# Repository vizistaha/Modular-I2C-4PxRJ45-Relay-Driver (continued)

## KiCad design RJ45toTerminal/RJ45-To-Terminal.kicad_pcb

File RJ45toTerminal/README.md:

# RJ45 To Terminal Mapping

| Pin        | Pair       | Color        | Terminal  | 
| ---------- |:----------:| ------------ | --------- | 
| 1          | 1+         | Orange-White | 1         | 
| 2          | 1-         | Orange       | 2         |
| 3          | 2+         | Green-White  | 3         |
| 6          | 2-         | Green        | 4         |
| 5          | 3+         | Blue-White   | 5         |
| 4          | 3-         | Blue         | 6         |
| 7          | 4+         | Brown-White  | 7         |
| 8          | 4-         | Brown        | 8         |

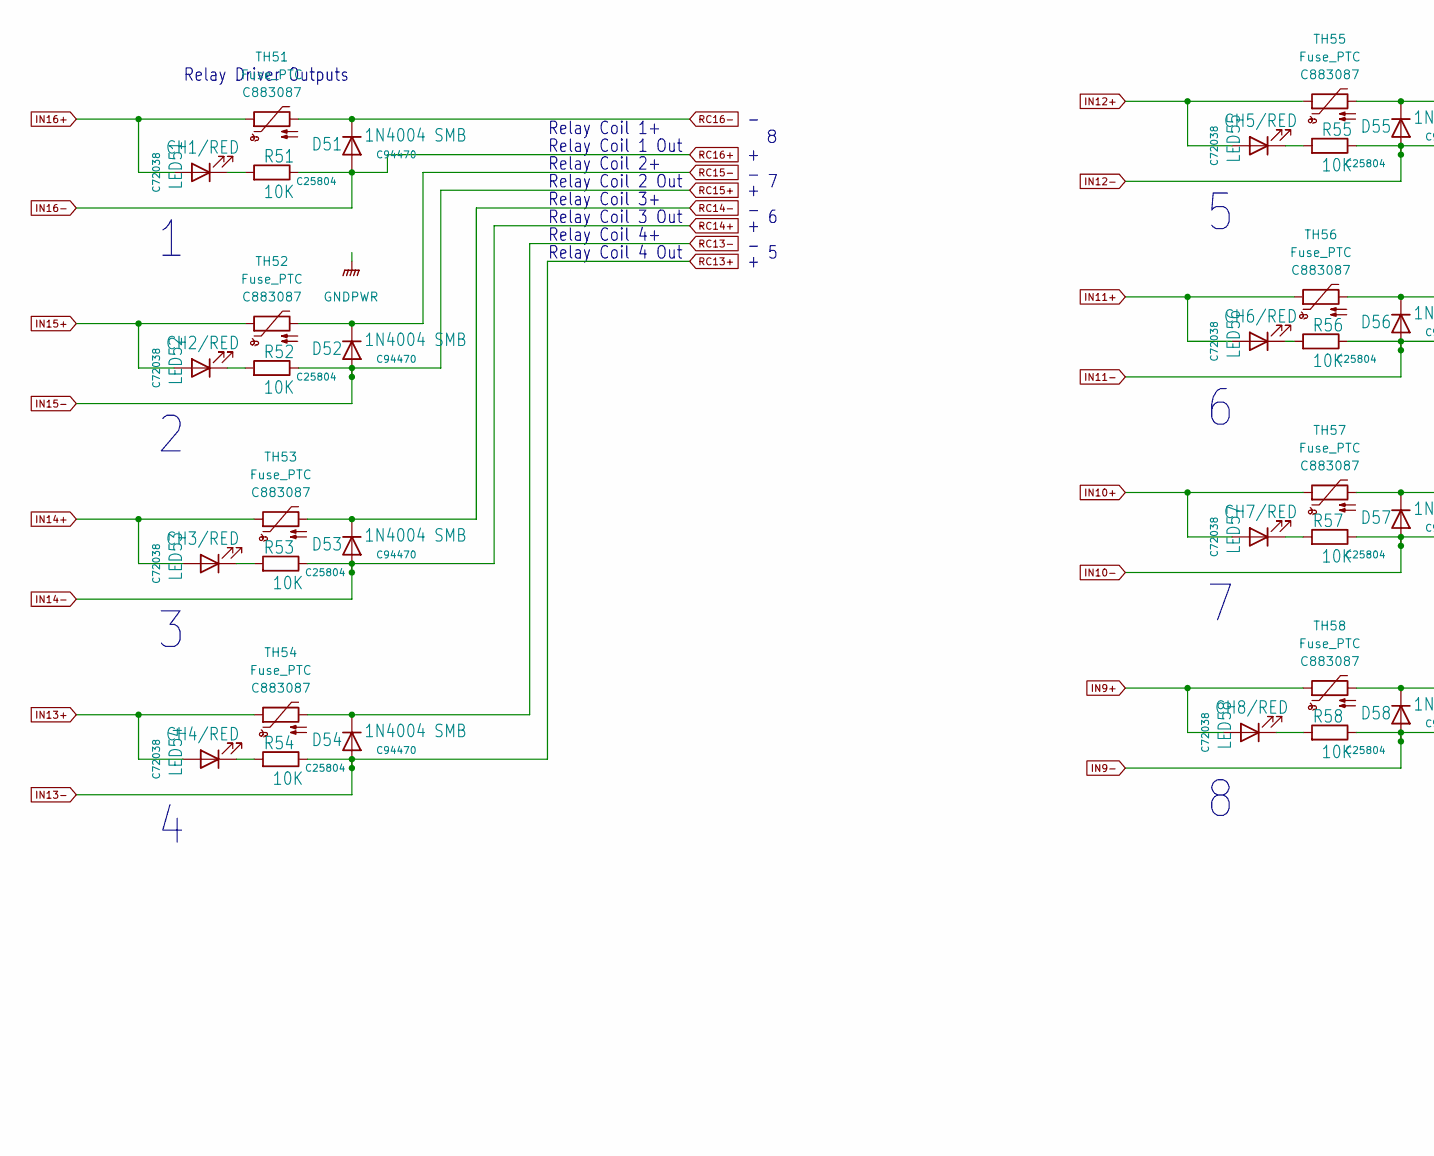
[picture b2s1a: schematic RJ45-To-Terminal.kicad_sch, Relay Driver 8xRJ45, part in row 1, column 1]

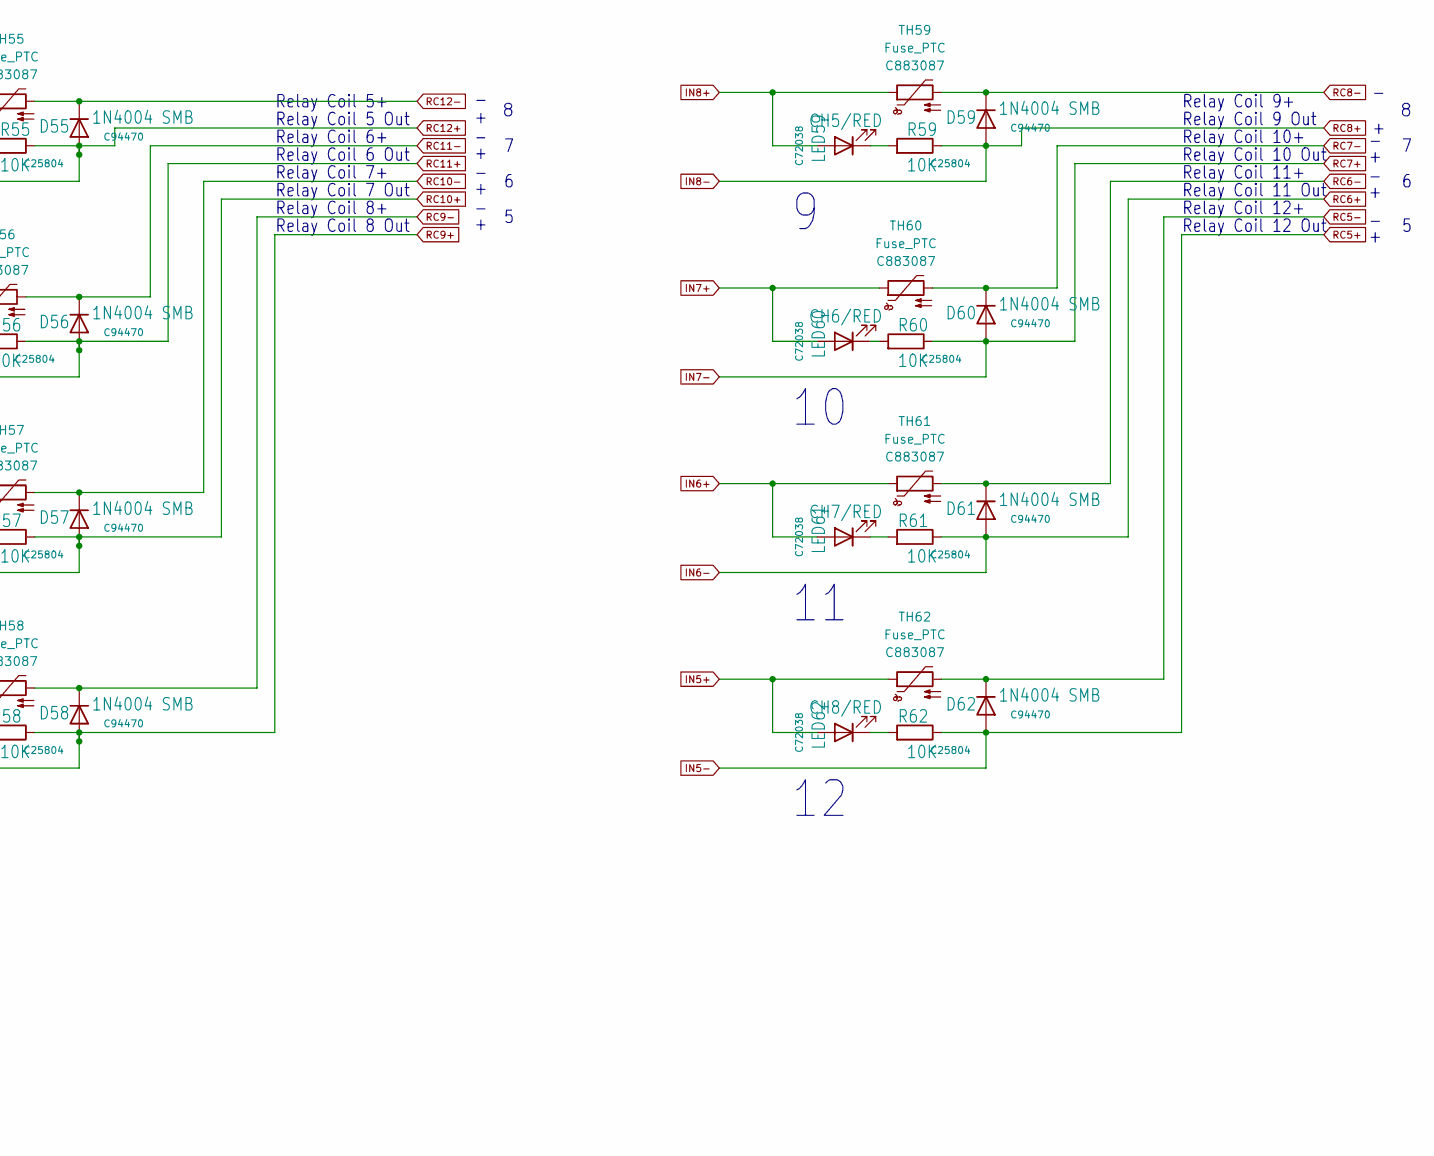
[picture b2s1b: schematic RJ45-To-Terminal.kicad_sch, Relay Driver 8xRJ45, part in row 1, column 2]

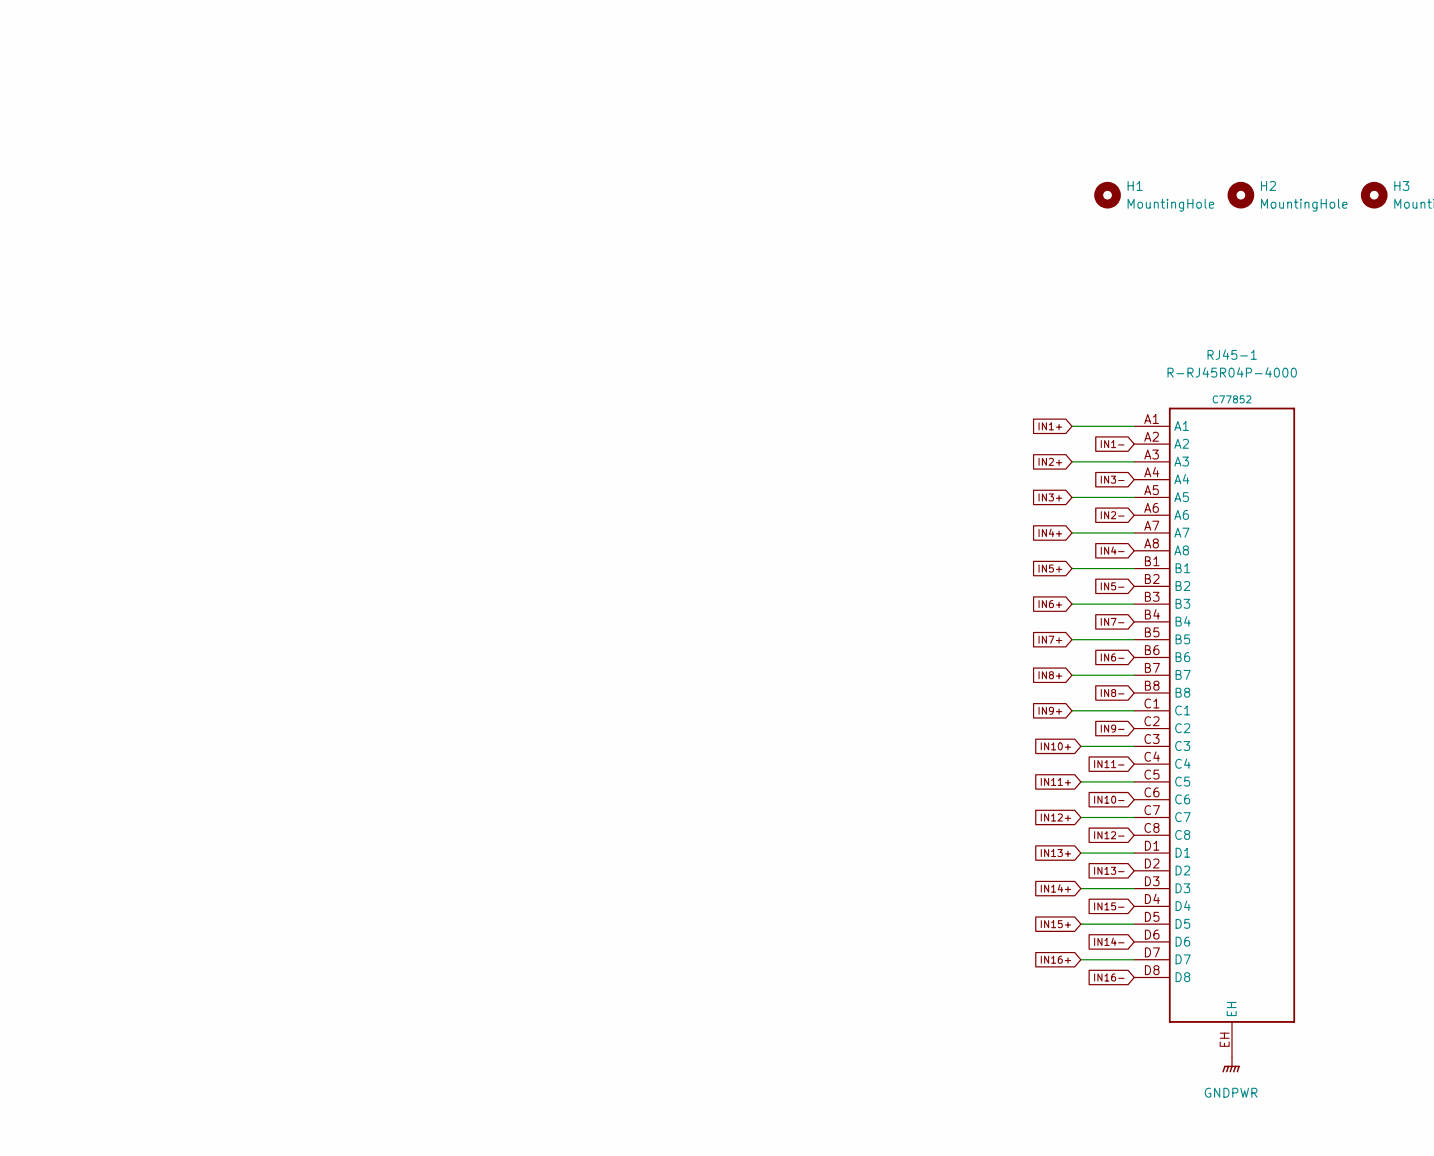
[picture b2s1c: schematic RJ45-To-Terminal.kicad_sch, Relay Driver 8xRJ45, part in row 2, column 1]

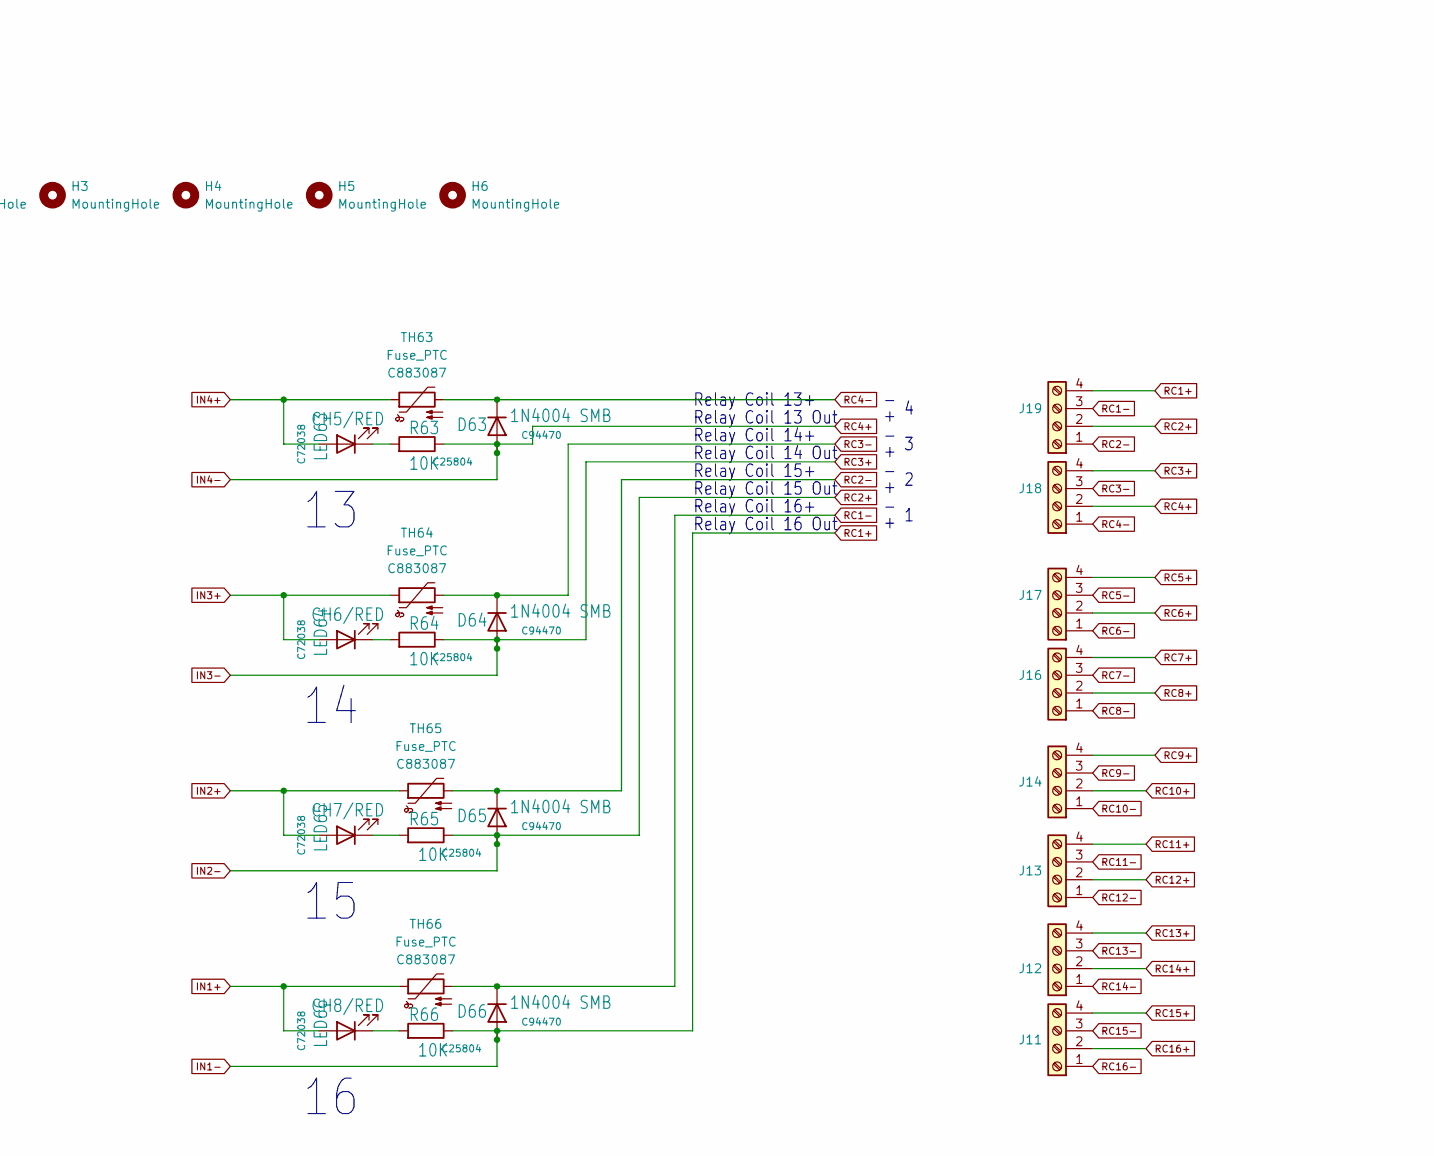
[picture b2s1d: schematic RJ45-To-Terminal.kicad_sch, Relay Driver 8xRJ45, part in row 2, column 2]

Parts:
D51, D52, D53, D54, D55, D56, D57, D58, D59, D60, D61, D62, D63, D64, D65, D66: 1N4004 SMB; D_MicroSMP; LCSC C94470
H1, H2, H3, H4, H5, H6: MountingHole; MountingHole_3.2mm_M3
J11, J13, J16, J18: Screw_Terminal_01x04; CONN-TH_XY2500V-F-3.5-4P; LCSC C880556
J12, J14, J17, J19: Screw_Terminal_01x04; CONN-TH_XY2500R-G-3.5-4P; LCSC C880574
LED51: CH1/RED; LED_0603_1608Metric; LCSC1 C72038
LED52: CH2/RED; LED_0603_1608Metric; LCSC1 C72038
LED53: CH3/RED; LED_0603_1608Metric; LCSC1 C72038
LED54: CH4/RED; LED_0603_1608Metric; LCSC1 C72038
LED55, LED59, LED63: CH5/RED; LED_0603_1608Metric; LCSC1 C72038
LED56, LED60, LED64: CH6/RED; LED_0603_1608Metric; LCSC1 C72038
LED57, LED61, LED65: CH7/RED; LED_0603_1608Metric; LCSC1 C72038
LED58, LED62, LED66: CH8/RED; LED_0603_1608Metric; LCSC1 C72038
R51, R52, R53, R54, R55, R56, R57, R58, R59, R60, R61, R62, R63, R64, R65, R66: 10K; R_0603_1608Metric; LCSC C25804
RJ45-1: R-RJ45R04P-4000; CONN-TH_DS1129-02-S80BP; LCSC C77852
TH51, TH52, TH53, TH54, TH55, TH56, TH57, TH58, TH59, TH60, TH61, TH62, TH63, TH64, TH65, TH66: Fuse_PTC; R_0603_1608Metric; LCSC C883087

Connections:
GNDPWR: RJ45-1.EH
IN1+: LED66.2 (A), RJ45-1.A1, TH66.1
IN1-: D66.2 (A), J19.4, R66.1, RJ45-1.A2
IN2+: LED65.2 (A), RJ45-1.A3, TH65.1
IN2-: D65.2 (A), J19.2, R65.1, RJ45-1.A6
IN3+: LED64.2 (A), RJ45-1.A5, TH64.1
IN3-: D64.2 (A), J18.4, R64.1, RJ45-1.A4
IN4+: LED63.2 (A), RJ45-1.A7, TH63.1
IN4-: D63.2 (A), J18.2, R63.1, RJ45-1.A8
IN5+: LED62.2 (A), RJ45-1.B1, TH62.1
IN5-: D62.2 (A), J17.4, R62.1, RJ45-1.B2
IN6+: LED61.2 (A), RJ45-1.B3, TH61.1
IN6-: D61.2 (A), J17.2, R61.1, RJ45-1.B6
IN7+: LED60.2 (A), RJ45-1.B5, TH60.1
IN7-: D60.2 (A), J16.4, R60.1, RJ45-1.B4
IN8+: LED59.2 (A), RJ45-1.B7, TH59.1
IN8-: D59.2 (A), J16.2, R59.1, RJ45-1.B8
IN9+: LED58.2 (A), RJ45-1.C1, TH58.1
IN9-: D58.2 (A), J14.4, R58.1, RJ45-1.C2
IN10+: LED57.2 (A), RJ45-1.C3, TH57.1
IN10-: D57.2 (A), J14.2, R57.1, RJ45-1.C6
IN11+: LED56.2 (A), RJ45-1.C5, TH56.1
IN11-: D56.2 (A), J13.4, R56.1, RJ45-1.C4
IN12+: LED55.2 (A), RJ45-1.C7, TH55.1
IN12-: D55.2 (A), J13.2, R55.1, RJ45-1.C8
IN13+: LED54.2 (A), RJ45-1.D1, TH54.1
IN13-: D54.2 (A), J12.4, R54.1, RJ45-1.D2
IN14+: LED53.2 (A), RJ45-1.D3, TH53.1
IN14-: D53.2 (A), J12.2, R53.1, RJ45-1.D6
IN15+: LED52.2 (A), RJ45-1.D5, TH52.1
IN15-: D52.2 (A), J11.4, R52.1, RJ45-1.D4
IN16+: LED51.2 (A), RJ45-1.D7, TH51.1
IN16-: D51.2 (A), J11.2, R51.1, RJ45-1.D8
unnamed: LED51.1 (K), R51.2
unnamed: LED52.1 (K), R52.2
unnamed: LED53.1 (K), R53.2
unnamed: LED54.1 (K), R54.2
unnamed: LED55.1 (K), R55.2
unnamed: LED56.1 (K), R56.2
unnamed: LED57.1 (K), R57.2
unnamed: LED58.1 (K), R58.2
unnamed: LED59.1 (K), R59.2
unnamed: LED60.1 (K), R60.2
unnamed: LED61.1 (K), R61.2
unnamed: LED62.1 (K), R62.2
unnamed: LED63.1 (K), R63.2
unnamed: LED64.1 (K), R64.2
unnamed: LED65.1 (K), R65.2
unnamed: LED66.1 (K), R66.2
RC1-: D66.1 (K), J19.3, TH66.2
RC2-: D65.1 (K), J19.1, TH65.2
RC3-: D64.1 (K), J18.3, TH64.2
RC4-: D63.1 (K), J18.1, TH63.2
RC5-: D62.1 (K), J17.3, TH62.2
RC6-: D61.1 (K), J17.1, TH61.2
RC7-: D60.1 (K), J16.3, TH60.2
RC8-: D59.1 (K), J16.1, TH59.2
RC9-: D58.1 (K), J14.3, TH58.2
RC10-: D57.1 (K), J14.1, TH57.2
RC11-: D56.1 (K), J13.3, TH56.2
RC12-: D55.1 (K), J13.1, TH55.2
RC13-: D54.1 (K), J12.3, TH54.2
RC14-: D53.1 (K), J12.1, TH53.2
RC15-: D52.1 (K), J11.3, TH52.2
RC16-: D51.1 (K), J11.1, TH51.2

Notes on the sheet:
Relay Coil 4+
Relay Coil 14 Out
Relay Coil 2+
Relay Driver Outputs
Relay Coil 13+
Relay Coil 1 Out
Relay Coil 7 Out
Relay Coil 10+
Relay Coil 16 Out
Relay Coil 15 Out
Relay Coil 12+
Relay Coil 12 Out
Relay Coil 7+
Relay Coil 13 Out
Relay Coil 1+
Relay Coil 3+
Relay Coil 15+
Relay Coil 14+
Relay Coil 8+
Relay Coil 11 Out
Relay Coil 4 Out
Relay Coil 3 Out
Relay Coil 6+
Relay Coil 6 Out
Relay Coil 2 Out
Relay Coil 5+
Relay Coil 5 Out
Relay Coil 9 Out
Relay Coil 10 Out
Relay Coil 16+
Relay Coil 9+
Relay Coil 11+
Relay Coil 8 Out

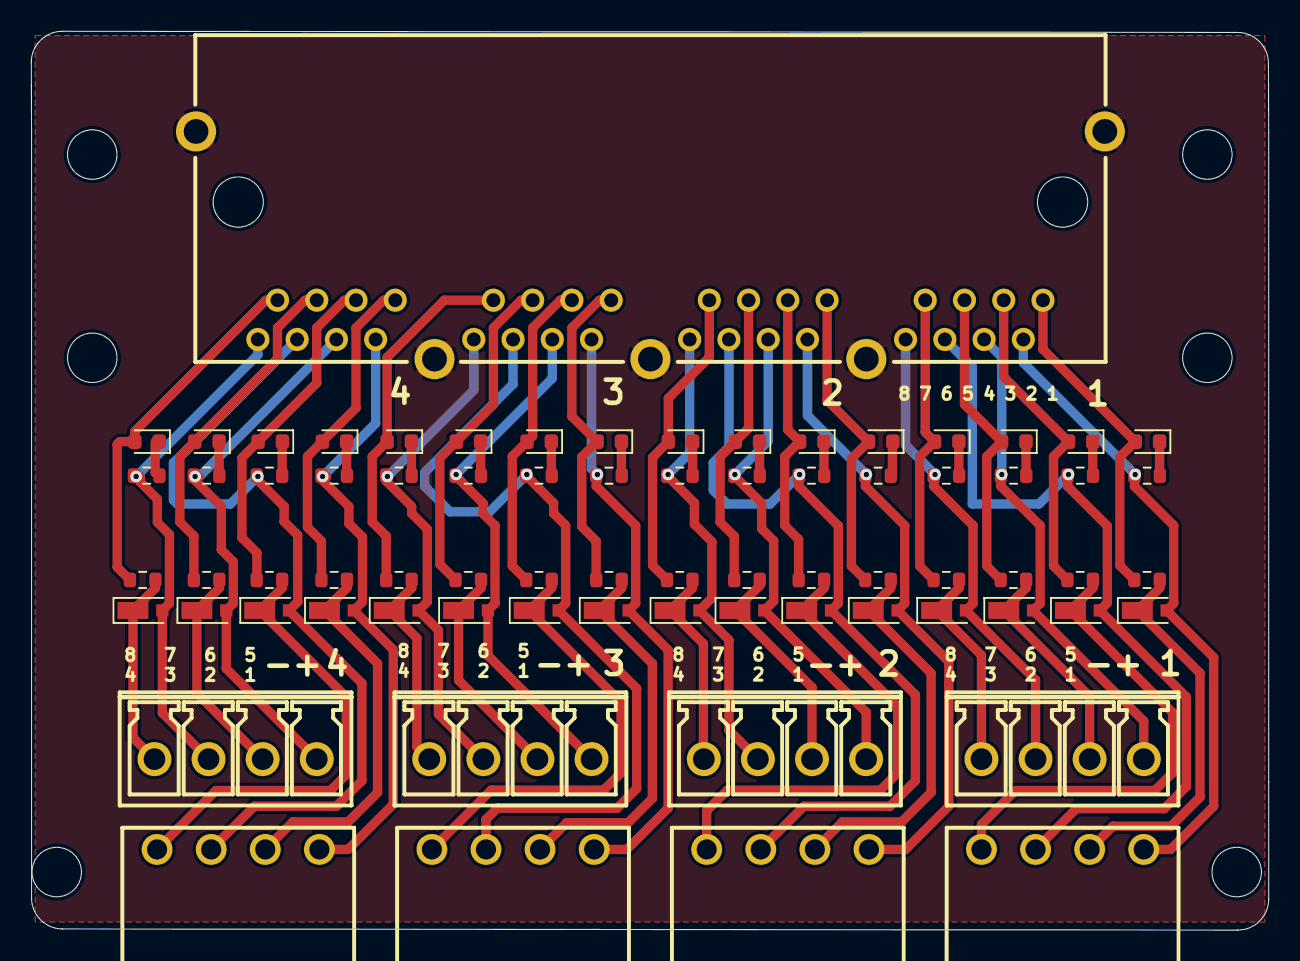
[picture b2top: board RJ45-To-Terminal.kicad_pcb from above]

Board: 2 copper layers, 80.1 x 58.2 mm, 79 parts (0 on the bottom side), 64 nets.

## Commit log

2023-11-01 init
2023-11-01 added release files
2023-11-01 added 3d model
2023-11-04 isolated
2023-11-04 optocoupler update
2023-11-05 added 3d models
2023-11-06 3d update, manufacturing files
2023-11-08 clean up
2023-11-09 production files
2023-11-09 images and fabrication files
2023-11-09 logo
2023-11-10 RJ45 to Pluggable break out
2023-11-10 read me update and label
2023-11-10 documents
2023-11-10 cleanup
2023-11-10 folder cleanup
2025-04-09 updated RJ45ToTerminal with additional space between pluggable conenctor
2025-07-28 updated to support 5V output for fan speed control in rev2
2025-10-06 5V input suport
2025-10-06 updated jumper read me
2025-10-08 Fixed foot print and lcsc part id
2025-10-08 fixes
2025-10-09 removed submodule
2025-10-09 added submodule
